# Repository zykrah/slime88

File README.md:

# Slime88 TKL PCB
 A F13 TKL Multi-Layout Hotswap H88-Compat Type-C PCB, designed in KiCAD 6.0.

**This board has now been prototyped! See IRL images below.**

> NOTE: Below images may be outdated.

Renders (KiCAD):

IRL images of rev1 protos:

## Features
- Fits the h88(c) standard (confirmed working in a KFE CE, should fit F13 frog)
- Uses the RP2040 MCU (new), with 16MB of external flash
- Uses Kailh Hotswap Sockets
- Added anti-shearing to the hotswap sockets
- Holes of hotswap socket holes are plated, you can still solder in a switch, should a hotswap socket ever shear off for whatever reason
- Multi-layout (see below)
- Removable USB-C connector, as well as a JST connector for [Unified Daughterboard](https://github.com/ai03-2725/Unified-Daughterboard) support (for F13 TKL boards that are compatible with the daughterboard version of the h88c)
- Has cutouts for a gummy o-ring mount (Same as the hineybush h88c pcb, for boards such as the Freebird TKL or TGR Jane V2 CE)
- BOOT pins/header for getting into bootloader (short the pins while plugging in) if [bootmagic](https://github.com/qmk/qmk_firmware/blob/master/docs/feature_bootmagic.md) isn't available . Acessible from both sides of the PCB, even when PCB is built in a keyboard. Just remove the **END key/switch** to access it.
- SWD header for debugging
- Has unused MCU GPIO pins broken out
- ESD chip (SRV05-4) to prevent damage from electrostatic discharge
- Polyfuse to prevent overcurrent
- Optimized for manufacturing and assembly with JLCPCB
- Bonus: Curved traces and teardrops

> Also, `Sleep-Lib` is just the library by [Sleepdealer](https://github.com/Sleepdealr), used in his [RP2040 Design guide](https://github.com/Sleepdealr/RP2040-designguide).

## Firmware
~~As of writing, the board runs the rp2040 branch/fork of vial-qmk. I will update this to use the official QMK implementation of RP2040 when it releases.~~ ~~UPDATE: RP2040 support has recently made it into QMK's `develop` branch. It will be fully merged to `master` by Q3 this year. Until then, the official maintainer of vial doesn't intend to merge those changes into their vial repo either, so I have made my own fork for the boards. When vial-qmk is officially updated to use QMK's implementiation of the RP2040, I will update this page once again linking to that, assuming I get the board merged into the official repo too.~~

You can find the up-to-date VIAL firmware [here](https://github.com/zykrah/vial-qmk/tree/vial-stable-zykrah/keyboards/zykrah/slime88). 

UPDATE: The board is now also in [qmk master](https://github.com/qmk/qmk_firmware/tree/master/keyboards/zykrah/slime88). (This particular version will only be VIA compatible). It should automatically be detected in VIA.

## WIP/Ideas
- Spare components on the board (i.e. diodes)
- Add physical reset switch (you currently have to short the pins on the SWD header manually)
- Add physical boot switch (you currently have to short the BOOT pins manually)
- Version with flex cuts (Already done but removed for acoustic reasons. See the board at [this point in time](https://github.com/zykrah/slime88/commit/3de3e59620d77a87f4beb085508b7e4e2e0daaf5))
- Update silkscreen graphics
- Add more layout indicators on the top silkscreen of the pcb
- Do something more special with USB shield/ground connection (currently shield is connected straight to ground)
- Move ESD chip to before fuse
- ~~Also breakout 3v3 and 5v on the pin breakout~~ Thanks [@vinorodrigues](https://github.com/vinorodrigues)!

## Multi-Layout Support

> NOTE: ANSI/ISO support works a little bit specially, either combination is soldered in at a time to ensure minimal R3 Cherry profile interference, and avoid having to rotate hotswap sockets 90 degrees to east/west orientation. See second image below.

## Removable USB C Port

Uses mousebites. Strength/functionality is untested.

## How to Manufacture the PCBs (JLCPCB)
~~I would personally use [this plugin](https://github.com/Bouni/kicad-jlcpcb-tools).~~

~~All components should be basic components, apart from the MCU, fuse, and JST connector (extended).~~

~~JLC also does have [kailh hotswap sockets](https://jlcpcb.com/parts/componentSearch?isSearch=true&searchTxt=C2803348) (extended) in its parts library, but you should be very careful with the ANSI/ISO multilayout support. In the BOM, only include either desired combination of sockets (or none of them, and hand solder in the ones you want).~~

The manufacturing files (JLCPCBA specific) have been added to the repo, you need to choose betweeen ANSI or ISO enter/pipe hotswap sockets being soldered by default.

You may want to consider generating the manufacturing files for yourself. I have not fully tested the ones that are currently in the repo.

> **NOTE: As the USB C connector is top-mounted (all other components are bottom mounted), as of writing, JLCPCB will charge extra to assemble the USB C connector (Standard assembly, both sides). You will likely have to hand solder it if you don't want to pay too much. Otherwise, seek out a proper PCB manufacturer (which will require further experience/knowledge).**

## Silkscreen
For the non-weebs, the silkscreen is based on Rimuru Tempest

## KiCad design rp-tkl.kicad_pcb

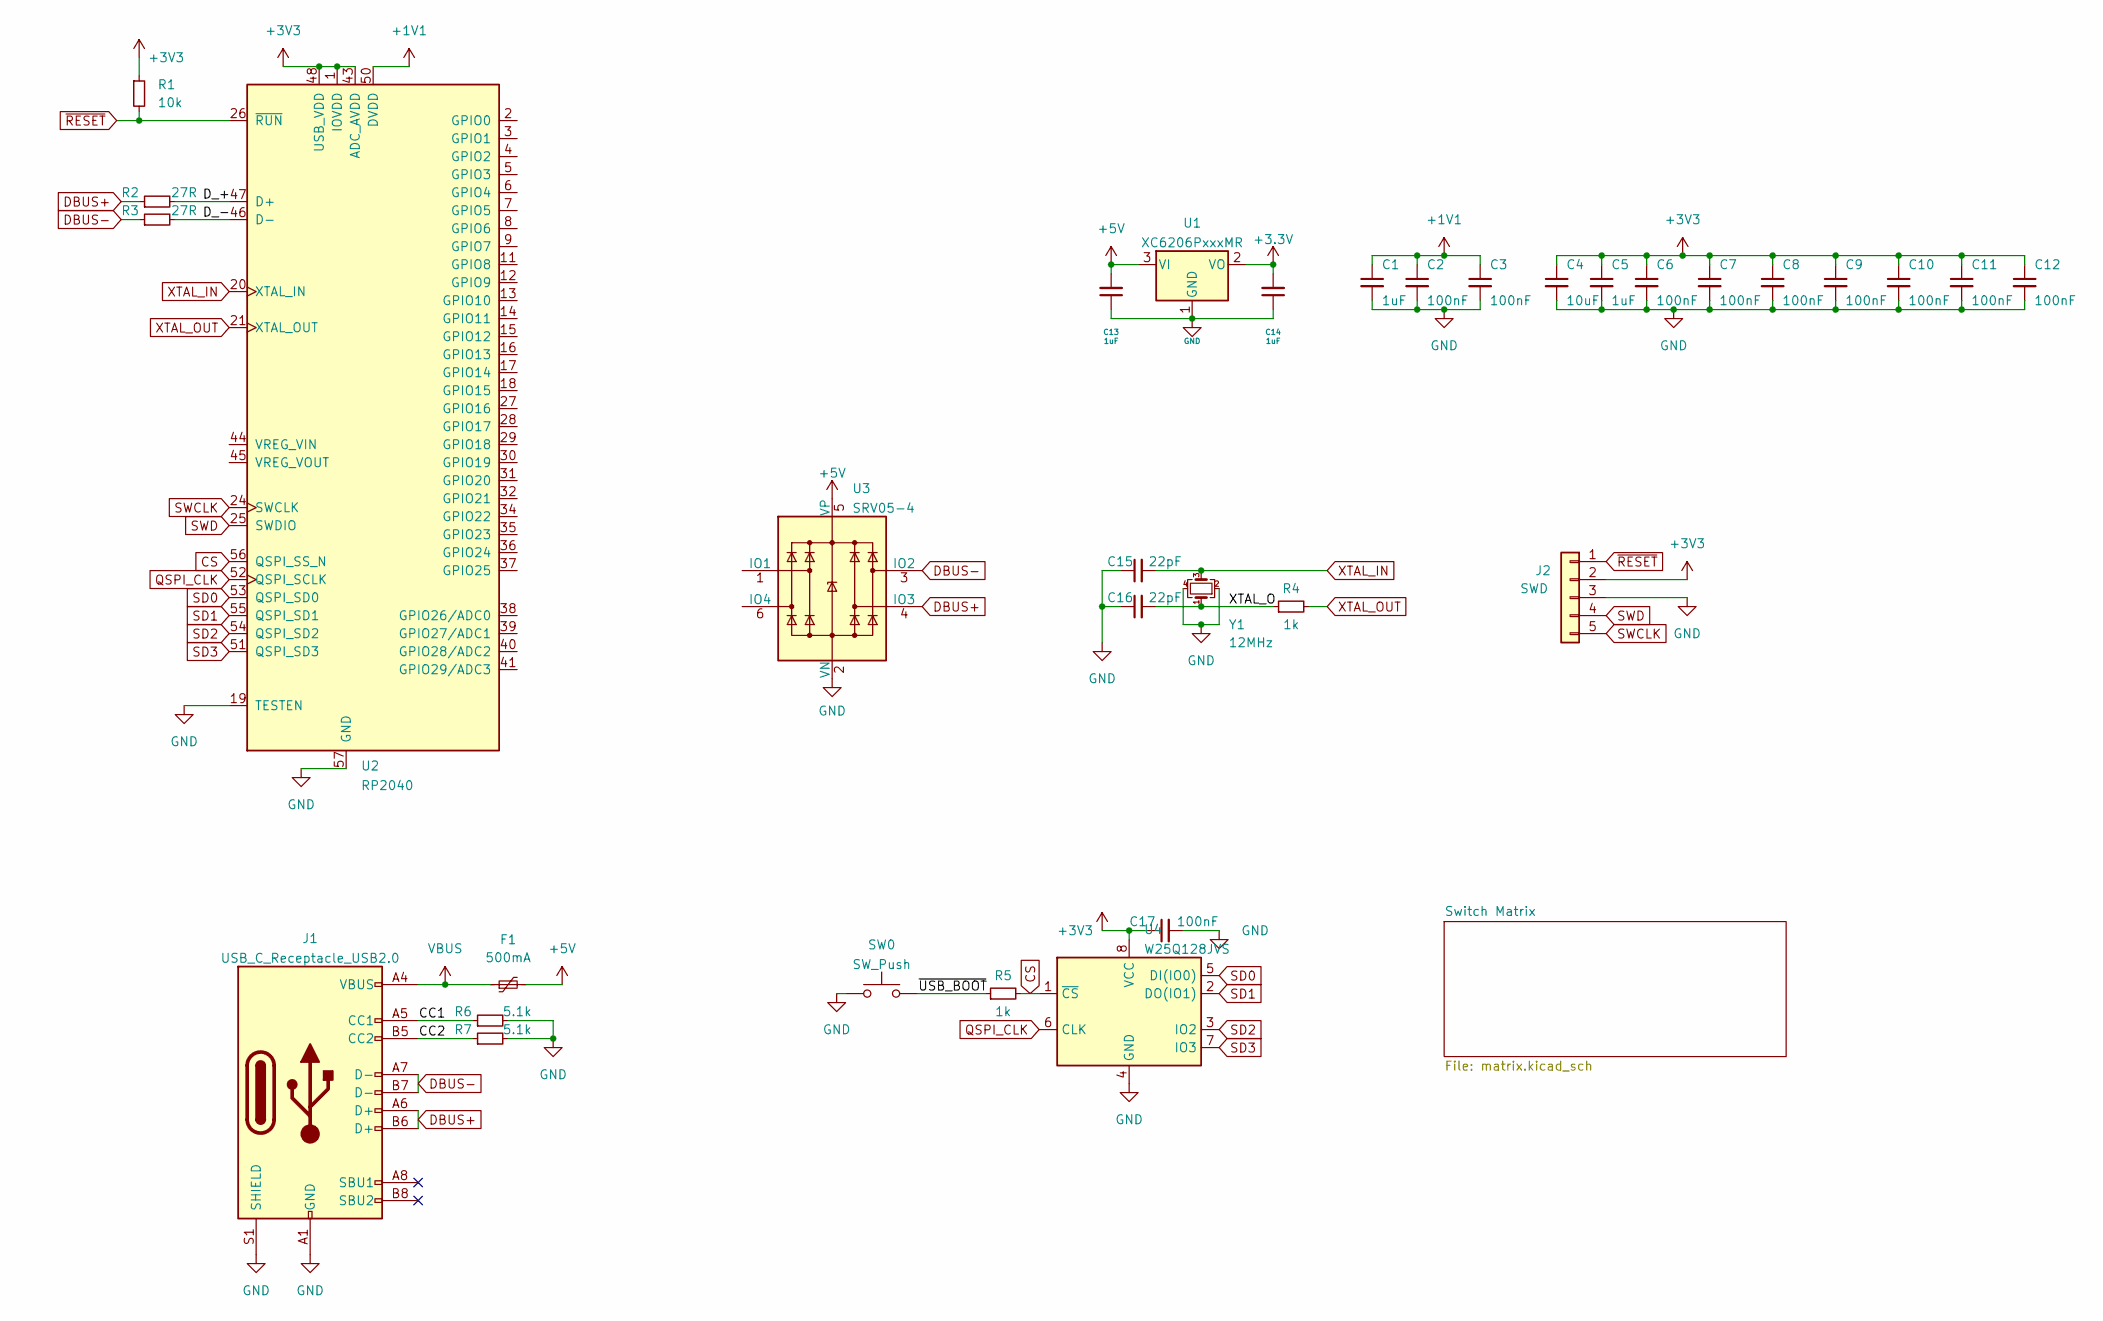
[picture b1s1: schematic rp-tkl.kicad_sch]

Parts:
C1, C5, C13, C14: 1uF; C_0402_1005Metric; LCSC C52923
C2, C3, C6, C7, C8, C9, C10, C11, C12, C17: 100nF; C_0402_1005Metric; LCSC C1525
C4: 10uF; C_0402_1005Metric; LCSC C15525
C15, C16: 22pF; C_0402_1005Metric; LCSC C1555
F1: 500mA; Fuse_1206_3216Metric; LCSC C70076
J1: USB_C_Receptacle_USB2.0; USB_C_Receptacle_HRO_TYPE-C-31-M-12
J2: SWD; PinSocket_1x05_P2.54mm_Vertical
R1: 10k; R_0402_1005Metric; LCSC C25744
R2, R3: 27R; R_0603_1608Metric; LCSC C25190
R4, R5: 1k; R_0402_1005Metric; LCSC C11702
R6, R7: 5.1k; R_0402_1005Metric; LCSC C25905
SW0: SW_Push; PinSocket_1x02_P2.54mm_Vertical
U1: XC6206PxxxMR; SOT-23
U2: RP2040; RP2040-QFN-56
U3: SRV05-4; SOT-23-6-routable
U4: W25Q128JVS; SOIC-8_5.23x5.23mm_P1.27mm
Y1: 12MHz; Crystal_SMD_3225-4Pin_3.2x2.5mm; LCSC C9002

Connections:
+1V1: C1.1, C2.1, C3.1, U2.23 (DVDD), U2.50 (DVDD)
+5V: C13.2, F1.2, U1.3 (VI), U3.5 (VP)
/CC1: J1.A5 (CC1), R6.1
/CC2: J1.B5 (CC2), R7.1
/D_+: R2.2, U2.47 (D+)
/D_-: R3.2, U2.46 (D-)
/XTAL_O: C16.2, R4.1, Y1.1
/~USB_BOOT: R5.1, SW0.2
CS: R5.2, U2.56 (QSPI_SS_N), U4.1 (~CS)
DBUS+: J1.A6 (D+), J1.B6 (D+), R2.1, U3.4 (IO3)
DBUS-: J1.A7 (D-), J1.B7 (D-), R3.1, U3.3 (IO2)
GND: C1.2, C2.2, C3.2, C4.2, C5.2, C6.2, C7.2, C8.2, C9.2, C10.2, C11.2, C12.2, C13.1, C14.1, C15.1, C16.1, C17.2, J1.A1 (GND), J1.A12 (GND), J1.B1 (GND), J1.B12 (GND), J1.S1 (SHIELD), J2.3, R6.2, R7.2, SW0.1, U1.1 (GND), U2.19 (TESTEN), U2.57 (GND), U3.2 (VN), U4.4 (GND), Y1.2, Y1.4
QSPI_CLK: U2.52 (QSPI_SCLK), U4.6 (CLK)
SD0: U2.53 (QSPI_SD0), U4.5 (DI(IO0))
SD1: U2.55 (QSPI_SD1), U4.2 (DO(IO1))
SD2: U2.54 (QSPI_SD2), U4.3 (IO2)
SD3: U2.51 (QSPI_SD3), U4.7 (IO3)
SWCLK: J2.5, U2.24 (SWCLK)
SWD: J2.4, U2.25 (SWDIO)
VBUS: F1.1, J1.A4 (VBUS), J1.A9 (VBUS), J1.B4 (VBUS), J1.B9 (VBUS)
XTAL_IN: C15.2, U2.20 (XTAL_IN), Y1.3
XTAL_OUT: R4.2, U2.21 (XTAL_OUT)
~RESET: J2.1, R1.2, U2.26 (~RUN)

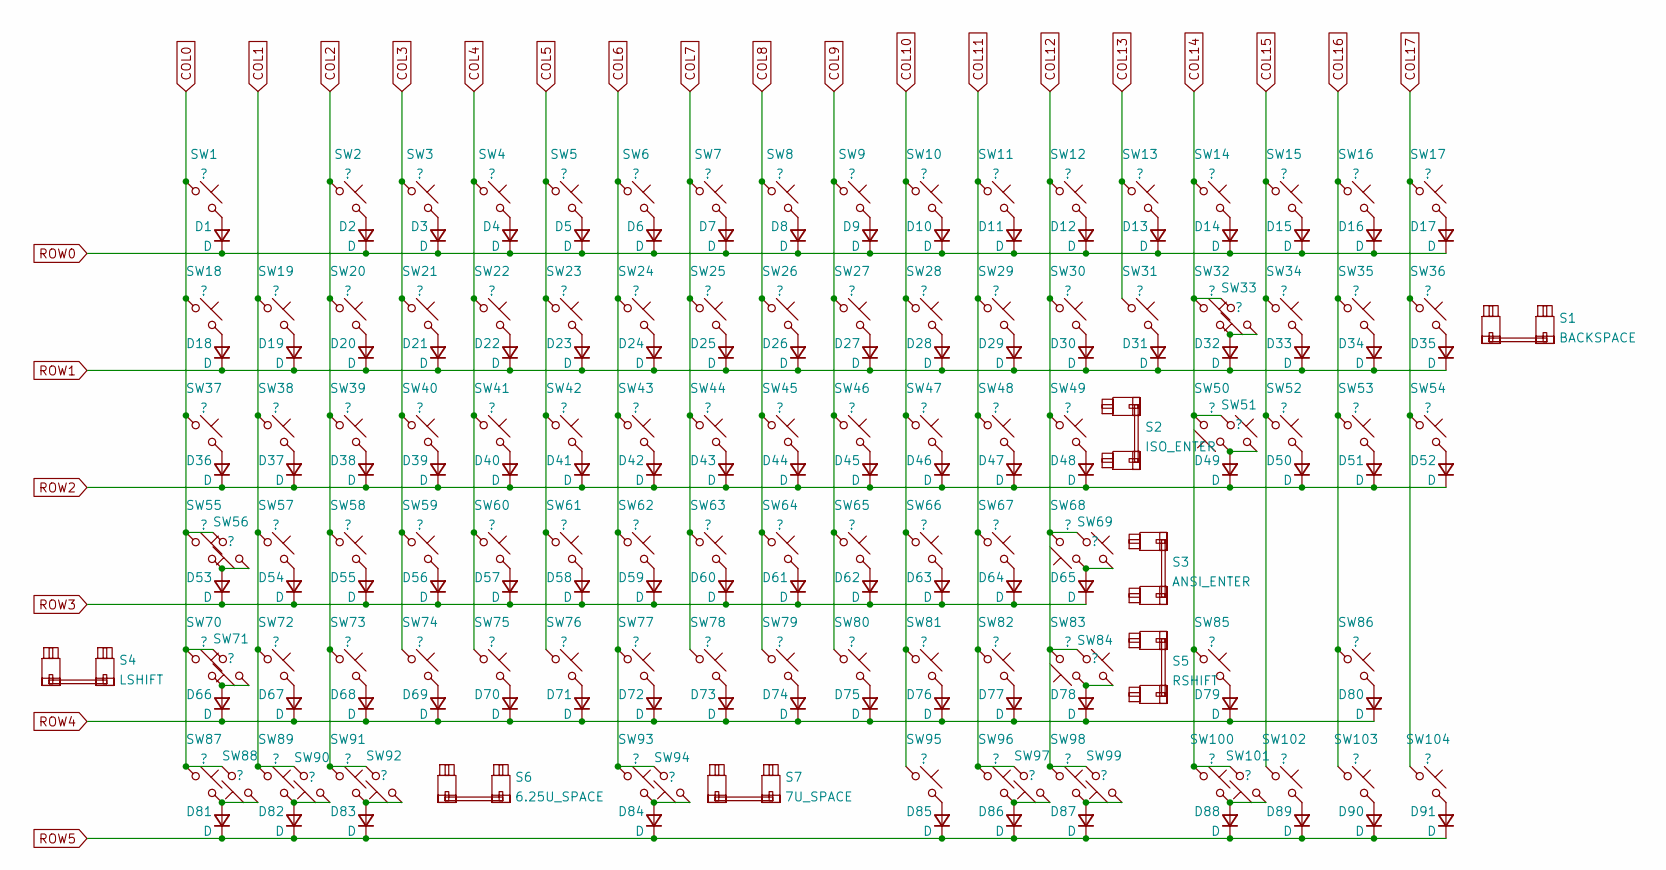
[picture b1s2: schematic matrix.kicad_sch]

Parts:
D1, D2, D3, D4, D5, D6, D7, D8, D9, D10, D11, D12, D13, D14, D15, D16, D17, D18, D19, D20, D21, D22, D23, D24, D25, D26, D27, D28, D29, D30, D31, D32, D33, D34, D35, D36, D37, D38, D39, D40, D41, D42, D43, D44, D45, D46, D47, D48, D49, D50, D51, D52, D53, D54, D55, D56, D57, D58, D59, D60, D61, D62, D63, D64, D65, D66, D67, D68, D69, D70, D71, D72, D73, D74, D75, D76, D77, D78, D79, D80, D81, D82, D83, D84, D85, D86, D87, D88, D89, D90, D91: D; D_SOD-123
S1: BACKSPACE; STAB_MX_2u
S2: ISO_ENTER; STAB_MX_ISO_FLIPPED
S3: ANSI_ENTER; STAB_MX_2.25u
S4: LSHIFT; STAB_MX_2.25u
S5: RSHIFT; STAB_MX_2.75u
S6: 6.25U_SPACE; STAB_MX_6.25u
S7: 7U_SPACE; STAB_MX_7u
SW1, SW2, SW3, SW4, SW5, SW6, SW7, SW8, SW9, SW10, SW11, SW12, SW13, SW14, SW15, SW16, SW17, SW18, SW19, SW20, SW21, SW22, SW23, SW24, SW25, SW26, SW27, SW28, SW29, SW30, SW31, SW32, SW33, SW34, SW35, SW36, SW38, SW39, SW40, SW41, SW42, SW43, SW44, SW45, SW46, SW47, SW48, SW49, SW51, SW52, SW53, SW54, SW57, SW58, SW59, SW60, SW61, SW62, SW63, SW64, SW65, SW66, SW67, SW68, SW69, SW71, SW72, SW73, SW74, SW75, SW76, SW77, SW78, SW79, SW80, SW81, SW82, SW84, SW85, SW86, SW90, SW93, SW94, SW98, SW102, SW103, SW104: ?; SW_MX_HS_1u
SW37, SW50, SW88, SW92, SW96, SW100: ?; SW_MX_HS_1.5u
SW55: ?; SW_MX_HS_1.75u_stp
SW56, SW83: ?; SW_MX_HS_1.75u
SW70, SW87, SW89, SW91, SW95, SW97, SW99, SW101: ?; SW_MX_HS_1.25u

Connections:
COL0: SW1.1, SW18.1, SW37.1, SW55.1, SW56.2, SW70.1, SW71.2, SW87.1, SW88.2
COL1: SW19.1, SW38.1, SW57.1, SW72.1, SW89.1, SW90.2
COL2: SW2.1, SW20.1, SW39.1, SW58.1, SW73.1, SW91.1, SW92.2
COL3: SW3.1, SW21.1, SW40.1, SW59.1, SW74.1
COL4: SW4.1, SW22.1, SW41.1, SW60.1, SW75.1
COL5: SW5.1, SW23.1, SW42.1, SW61.1, SW76.1
COL6: SW6.1, SW24.1, SW43.1, SW62.1, SW77.1, SW93.1, SW94.2
COL7: SW7.1, SW25.1, SW44.1, SW63.1, SW78.1
COL8: SW8.1, SW26.1, SW45.1, SW64.1, SW79.1
COL9: SW9.1, SW27.1, SW46.1, SW65.1, SW80.1
COL10: SW10.1, SW28.1, SW47.1, SW66.1, SW81.1, SW95.1
COL11: SW11.1, SW29.1, SW48.1, SW67.1, SW82.1, SW96.1, SW97.2
COL12: SW12.1, SW30.1, SW49.1, SW68.2, SW69.1, SW83.2, SW84.1, SW98.1, SW99.2
COL13: SW13.1, SW31.1
COL14: SW14.1, SW32.1, SW33.2, SW50.2, SW51.1, SW85.1, SW100.1, SW101.2
COL15: SW15.1, SW34.1, SW52.1, SW102.1
COL16: SW16.1, SW35.1, SW53.1, SW86.1, SW103.1
COL17: SW17.1, SW36.1, SW54.1, SW104.1
unnamed: D1.2 (A), SW1.2
unnamed: D2.2 (A), SW2.2
unnamed: D3.2 (A), SW3.2
unnamed: D4.2 (A), SW4.2
unnamed: D5.2 (A), SW5.2
unnamed: D6.2 (A), SW6.2
unnamed: D7.2 (A), SW7.2
unnamed: D8.2 (A), SW8.2
unnamed: D9.2 (A), SW9.2
unnamed: D10.2 (A), SW10.2
unnamed: D11.2 (A), SW11.2
unnamed: D12.2 (A), SW12.2
unnamed: D13.2 (A), SW13.2
unnamed: D14.2 (A), SW14.2
unnamed: D15.2 (A), SW15.2
unnamed: D16.2 (A), SW16.2
unnamed: D17.2 (A), SW17.2
unnamed: D18.2 (A), SW18.2
unnamed: D19.2 (A), SW19.2
unnamed: D20.2 (A), SW20.2
unnamed: D21.2 (A), SW21.2
unnamed: D22.2 (A), SW22.2
unnamed: D23.2 (A), SW23.2
unnamed: D24.2 (A), SW24.2
unnamed: D25.2 (A), SW25.2
unnamed: D26.2 (A), SW26.2
unnamed: D27.2 (A), SW27.2
unnamed: D28.2 (A), SW28.2
unnamed: D29.2 (A), SW29.2
unnamed: D30.2 (A), SW30.2
unnamed: D31.2 (A), SW31.2
unnamed: D32.2 (A), SW32.2, SW33.1
unnamed: D33.2 (A), SW34.2
unnamed: D34.2 (A), SW35.2
unnamed: D35.2 (A), SW36.2
unnamed: D36.2 (A), SW37.2
unnamed: D37.2 (A), SW38.2
unnamed: D38.2 (A), SW39.2
unnamed: D39.2 (A), SW40.2
unnamed: D40.2 (A), SW41.2
unnamed: D41.2 (A), SW42.2
unnamed: D42.2 (A), SW43.2
unnamed: D43.2 (A), SW44.2
unnamed: D44.2 (A), SW45.2
unnamed: D45.2 (A), SW46.2
unnamed: D46.2 (A), SW47.2
unnamed: D47.2 (A), SW48.2
unnamed: D48.2 (A), SW49.2
unnamed: D49.2 (A), SW50.1, SW51.2
unnamed: D50.2 (A), SW52.2
unnamed: D51.2 (A), SW53.2
unnamed: D52.2 (A), SW54.2
unnamed: D53.2 (A), SW55.2, SW56.1
unnamed: D54.2 (A), SW57.2
unnamed: D55.2 (A), SW58.2
unnamed: D56.2 (A), SW59.2
unnamed: D57.2 (A), SW60.2
unnamed: D58.2 (A), SW61.2
unnamed: D59.2 (A), SW62.2
unnamed: D60.2 (A), SW63.2
unnamed: D61.2 (A), SW64.2
unnamed: D62.2 (A), SW65.2
unnamed: D63.2 (A), SW66.2
unnamed: D64.2 (A), SW67.2
unnamed: D65.2 (A), SW68.1, SW69.2
unnamed: D66.2 (A), SW70.2, SW71.1
unnamed: D67.2 (A), SW72.2
unnamed: D68.2 (A), SW73.2
unnamed: D69.2 (A), SW74.2
unnamed: D70.2 (A), SW75.2
unnamed: D71.2 (A), SW76.2
unnamed: D72.2 (A), SW77.2
unnamed: D73.2 (A), SW78.2
unnamed: D74.2 (A), SW79.2
unnamed: D75.2 (A), SW80.2
unnamed: D76.2 (A), SW81.2
unnamed: D77.2 (A), SW82.2
unnamed: D78.2 (A), SW83.1, SW84.2
unnamed: D79.2 (A), SW85.2
unnamed: D80.2 (A), SW86.2
unnamed: D81.2 (A), SW87.2, SW88.1
unnamed: D82.2 (A), SW89.2, SW90.1
unnamed: D83.2 (A), SW91.2, SW92.1
unnamed: D84.2 (A), SW93.2, SW94.1
unnamed: D85.2 (A), SW95.2
unnamed: D86.2 (A), SW96.2, SW97.1
unnamed: D87.2 (A), SW98.2, SW99.1
unnamed: D88.2 (A), SW100.2, SW101.1
unnamed: D89.2 (A), SW102.2
unnamed: D90.2 (A), SW103.2
unnamed: D91.2 (A), SW104.2
ROW0: D1.1 (K), D2.1 (K), D3.1 (K), D4.1 (K), D5.1 (K), D6.1 (K), D7.1 (K), D8.1 (K), D9.1 (K), D10.1 (K), D11.1 (K), D12.1 (K), D13.1 (K), D14.1 (K), D15.1 (K), D16.1 (K), D17.1 (K)
ROW1: D18.1 (K), D19.1 (K), D20.1 (K), D21.1 (K), D22.1 (K), D23.1 (K), D24.1 (K), D25.1 (K), D26.1 (K), D27.1 (K), D28.1 (K), D29.1 (K), D30.1 (K), D31.1 (K), D32.1 (K), D33.1 (K), D34.1 (K), D35.1 (K)
ROW2: D36.1 (K), D37.1 (K), D38.1 (K), D39.1 (K), D40.1 (K), D41.1 (K), D42.1 (K), D43.1 (K), D44.1 (K), D45.1 (K), D46.1 (K), D47.1 (K), D48.1 (K), D49.1 (K), D50.1 (K), D51.1 (K), D52.1 (K)
ROW3: D53.1 (K), D54.1 (K), D55.1 (K), D56.1 (K), D57.1 (K), D58.1 (K), D59.1 (K), D60.1 (K), D61.1 (K), D62.1 (K), D63.1 (K), D64.1 (K), D65.1 (K)
ROW4: D66.1 (K), D67.1 (K), D68.1 (K), D69.1 (K), D70.1 (K), D71.1 (K), D72.1 (K), D73.1 (K), D74.1 (K), D75.1 (K), D76.1 (K), D77.1 (K), D78.1 (K), D79.1 (K), D80.1 (K)
ROW5: D81.1 (K), D82.1 (K), D83.1 (K), D84.1 (K), D85.1 (K), D86.1 (K), D87.1 (K), D88.1 (K), D89.1 (K), D90.1 (K), D91.1 (K)

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
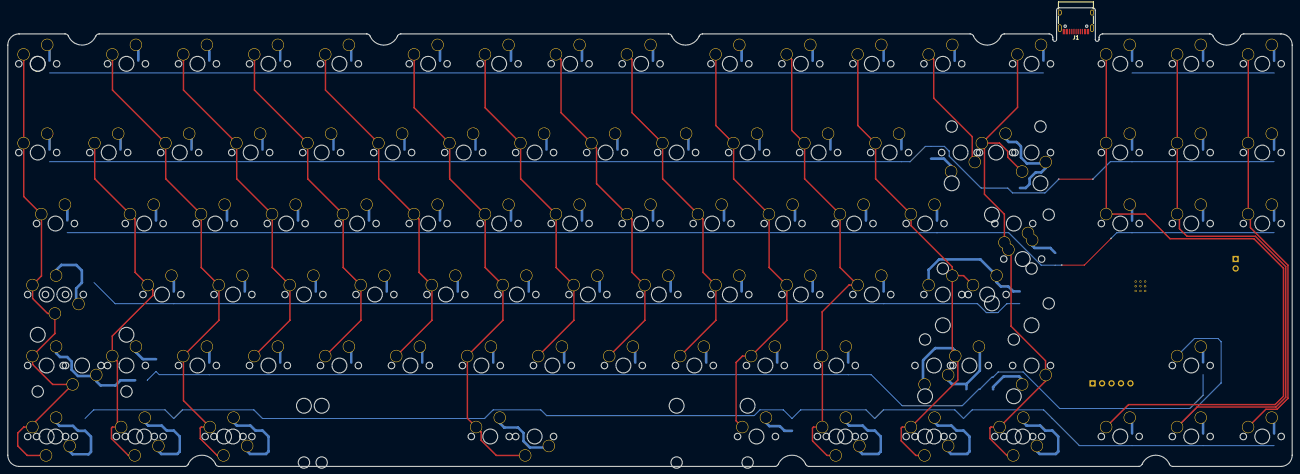
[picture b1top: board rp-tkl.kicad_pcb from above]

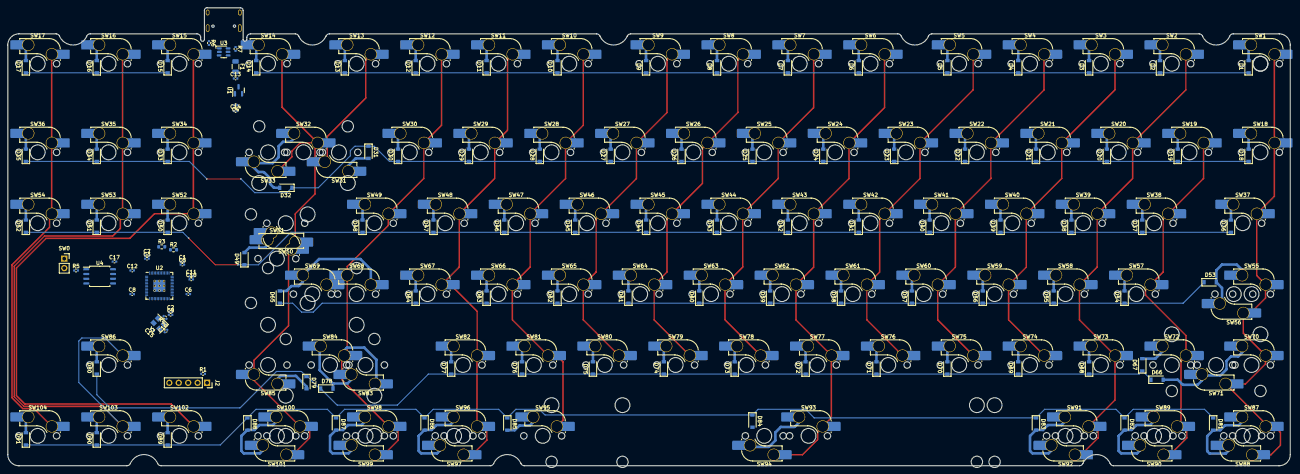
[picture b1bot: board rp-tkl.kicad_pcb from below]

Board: 2 copper layers, 344.7 x 123.1 mm, 235 parts (227 on the bottom side), 139 nets.

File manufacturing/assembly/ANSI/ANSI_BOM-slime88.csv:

Comment,Designator,Footprint,LCSC
1k,"R4,R5",R_0402_1005Metric,C11702
JST-SH-4P,J3,JST_SH_SM04B-SRSS-TB_1x04-1MP_P1.00mm_Horizontal,C145956
100nF,"C10,C11,C12,C17,C2,C3,C6,C7,C8,C9",C_0402_1005Metric,C1525
10uF,C4,C_0402_1005Metric,C15525
22pF,"C15,C16",C_0402_1005Metric,C1555
USB_C,J1,USB_C_Receptacle_HRO_TYPE-C-31-M-12,C165948
RP2040,U2,RP2040-QFN-56,C2040
27R,"R2,R3",R_0603_1608Metric,C25190
10k,R1,R_0402_1005Metric,C25744
5.1k,"R6,R7",R_0402_1005Metric,C25905
?,"SW1,SW10,SW100,SW101,SW102,SW103,SW104,SW11,SW12,SW13,SW14,SW15,SW16,SW17,SW18,SW19,SW2,SW20,SW21,SW22,SW23,SW24,SW25,SW26,SW27,SW28,SW29,SW3,SW30,SW31,SW32,SW33,SW34,SW35,SW36,SW37,SW38,SW39,SW4,SW40,SW41,SW42,SW43,SW44,SW45,SW46,SW47,SW48,SW49,SW5,SW50,SW52,SW53,SW54,SW55,SW56,SW57,SW58,SW59,SW6,SW60,SW61,SW62,SW63,SW64,SW65,SW66,SW67,SW69,SW7,SW70,SW71,SW72,SW73,SW74,SW75,SW76,SW77,SW78,SW79,SW8,SW80,SW81,SW82,SW83,SW84,SW85,SW86,SW87,SW88,SW89,SW9,SW90,SW91,SW92,SW93,SW94,SW95,SW96,SW97,SW98,SW99",SW_MX_HS_1u,C5156480
1uF,"C1,C13,C14,C5",C_0402_1005Metric,C52923
XC6206,U1,SOT-23,C5446
500mA,F1,Fuse_1206_3216Metric,C70076
D,"D1,D10,D11,D12,D13,D14,D15,D16,D17,D18,D19,D2,D20,D21,D22,D23,D24,D25,D26,D27,D28,D29,D3,D30,D31,D32,D33,D34,D35,D36,D37,D38,D39,D4,D40,D41,D42,D43,D44,D45,D46,D47,D48,D49,D5,D50,D51,D52,D53,D54,D55,D56,D57,D58,D59,D6,D60,D61,D62,D63,D64,D65,D66,D67,D68,D69,D7,D70,D71,D72,D73,D74,D75,D76,D77,D78,D79,D8,D80,D81,D82,D83,D84,D85,D86,D87,D88,D89,D9,D90,D91",D_SOD-123,"C81598
"
SRV05-4,U3,SOT-23-6-routable,C85364
12MHz,Y1,Crystal_SMD_3225-4Pin_3.2x2.5mm,C9002
W25Q128JVS,U4,SOIC-8_5.23x5.23mm_P1.27mm,C97521

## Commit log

2022-03-19 Added Git Ignore
2022-03-19 KiCAD project initialization
2022-03-19 Added Submodules
    marbastlib & Ai03
2022-03-19 Added RP2040 libraries
    Courtesy of https://github.com/Sleepdealr/RP2040-designguide
2022-03-19 Added main component symbols and PCB Outline
2022-03-19 Finished most of preliminary schematic
2022-03-19 Added Footprint Libs, Annotated schematic, Imported footprints
2022-03-19 [Excluding Switches] Moved components to rough positions on pcb
    Also added 5 pin programming header
2022-03-19 [Preliminary] Added Switch matrix and imported footprints
2022-03-19 Added Stabilizers
2022-03-19 All switches (not diodes) in position
2022-03-19 [Preliminary] Positioned diodes
2022-03-19 Changed Diodes to sod123
2022-03-19 Fixed some 3D models not showing
2022-03-19 [Preliminary] Matrix routed
2022-03-19 Further work on routing
    Added GND fills, wired USB more
    Need to do:
    MCU area
2022-03-22 Minor bug fixes
2022-03-22 [Preliminary] Completed MCU Routing
    - Also added some small things that i forgot on schematic
    - Need to: connect matrix to mcu
2022-03-22 [Preliminary] Traced rough estimate of how rows and columns will connect to pins
2022-03-22 [Preliminary] Completed all routing
2022-03-22 Minor cleanup work
2022-03-24 [70% Done] Rounded all traces
2022-03-24 More minor cleanup, DRC fixes
2022-03-25 [99% Done] Trace rounding and cleanup
2022-03-31 Added JST Connector
    Also cleaned up everything, 99% done
2022-03-31 More cleanup, added connector for/broke out unused pins
2022-03-31 [Temp] Mostly finalized, added teardrops
2022-03-31 More minor changes
    Added a ground pad to the unused pin breakout
2022-03-31 More minor changes
2022-03-31 Cleaned up silkscreen and fab layers
    Also adjusted some of the component descriptions/names
2022-04-02 [Big changes] Added flex cuts and changed switch matrix/ pinout
    - Optimized switch matrix by changing how the split backspace is done. It now connects to a different row instead of creating a whole different column
    - Shifted a lot of traces/pins over by one, slight retracing work around the mcu area
    - Added one more pin to the unused pins header
    - Added 2 simple flex cuts
    - Slight shifting around of different diodes
    - Added 3d model for JST and USB-C Connector
2022-04-03 Changed position of upper flex cut
    Didn't remove the old traces yet
2022-04-14 Lots of minor changes (some important changes)
    - Re-routed a lot of traces to the left of MCU
    - changed the rounding of some traces
    - changed the layout and rotation of some of the switch footprints/stabilizers to better reflect h88c
    - [IMPORTANT] changed minimum via size to 0.3/0.6 as per JLC spec
    - added bunch of random vias to via stitch GND fills
2022-04-17 Removed flex cut, updated outline and usb placement
    Also:
    - updated plugin config
    - changed pullup resistor placement and routing of some of the switch matrix (moved down row traces)
    - changed around some routing of the decoupling caps
    - added more stitching vias
2022-04-20 DRC fixes
    - changed the layer of the dimensions (they were on B.Cu before)
    - fixed some vias which were still 0.2/0.4
    - fixed some traces slightly too close to eachother
    - fixed some silkscreens
2022-04-20 Added some anti-shear vias
    (not intended for PCB assembly)
2022-04-20 (Minor fix) removed some anti-shear vias that were outside of edge cutout
2022-04-20 Added traces to the anti-shear (on the front)
    Just for aesthetics
2022-04-29 More minor changes
    I forgor
2022-04-29 Added mousebites to USB connector, some rerouting
    - Added mousebites next to the USB c connector area so the USB port is now more easily removeable.
    - Rerouted some of the USB area as a result of the above change
    - Modified USB silkscreen a bit (removed some lines)
    - Changed minimum trace width
    - Updated ESC and TILDE footprints to have a shorter pad so it doesn't go off the edge of the pcb. Did something similar for the F13 key because it was a bit close to the mousebites
2022-04-30 Fixed antishear vias, added multi-layout markings to silkscreen
    - Fixed the anti-shear vias (they were too small before; from 0.2/0.4 to 0.3/0.6)
    - Added some basic silkscreen to mark multi-layouts
2022-04-30 Fixed 3D models
    - hid the ISO hotswap socket 3d models
    - added all missing 3d models
2022-04-30 Minor changes to column traces
2022-05-27 Changed 1v1, Added silkscreen graphics
    - Named board Slime88
    - Changed internal 1v1 tracing a little bit
    - Added front and back graphics (stolen from one of my older boards)
    - Added RP logo and QMK badge
    - Added silkscreen labels to the pin breakout, SWD and boot pins.
    - :peepoSmile:
2022-05-29 Removed peepoSmile
    Sorry
2022-05-29 Renamed KiCAD project to slime88
    weeb
2022-05-29 Update README.md
    Credited Sleepdealr for RP2040 footprint/symbol library.
2022-05-29 Updated PCB silkscreen, gitignore, README
    Added github link to pcb silkscreen (on the back)
2022-05-29 Updated BOM inclusions
2022-05-30 Broke out 3v3 and 5v on Pin Breakout
    Suggested by https://github.com/vinorodrigues
    Slightly changed silkscreen (SWD -> SWDIO, Added boot indicator on the top silk)
    Rewired some of the matrix to appropriately fit the 3v3 and 5v traces.
2022-05-30 Updated Images, WIP
2022-05-30 Mention feature: BOOT header/pins
2022-05-30 Minor shift of gnd vias
2022-06-11 Update License to CERN OHL
2022-07-13 Update README.md, changed firmware link
2023-01-04 Generated manufacturing files (JLC), Updated Sleep-lib to a submodule, updated manufacturing files/part numbers
2023-01-04 Updated RP2040 3D model path
2023-01-04 Updated Manufacturing info
2023-01-27 Added Support Link :)
2023-05-02 Update README.md
    Updated firmware link
